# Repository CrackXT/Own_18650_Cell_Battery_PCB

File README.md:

# Own_18650_Cell_Battery_PCB

PCB files for a 18650 cell mount on a separate board

# Description

Compatible with protected 18650 cell type only!

This is an external battery cell board that allows you to mount the appropriate cell holder (18650) and thus have better connection and mounting options in your project or case.

The board can be produced here (AISLER) with the files (.brd and .sch) or by any other PCB manufacturer. -> https://aisler.net/

# Serie

- x

# Layout

Top<br>

Bottom<br>

Routing/Dimensions(inch)<br>

Schematic<br>
Schematic as .pdf at the top of the page.

# License

Open hardware, use it, mod it, whatever you want, feel free...

# Thanks!

Own design and layout.

# Version - Build

v1.3 - 18.06.2022

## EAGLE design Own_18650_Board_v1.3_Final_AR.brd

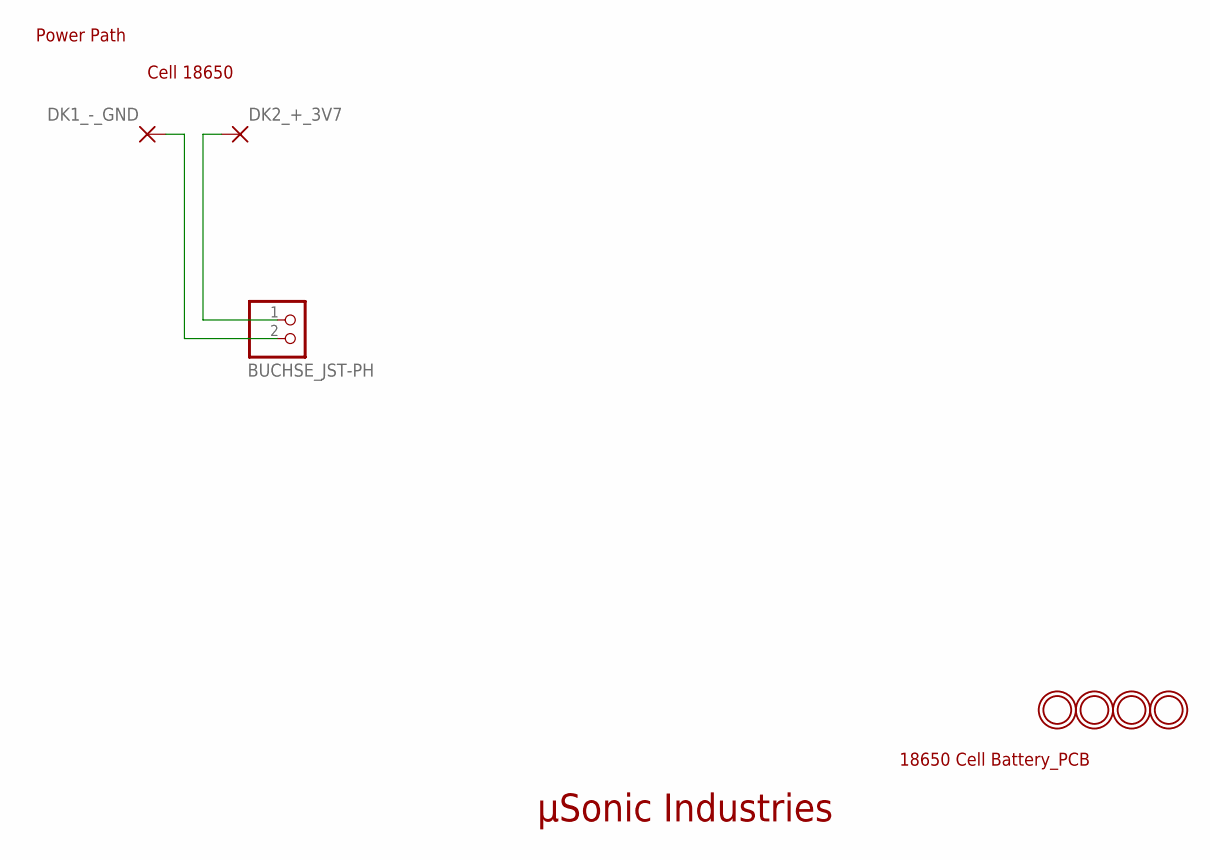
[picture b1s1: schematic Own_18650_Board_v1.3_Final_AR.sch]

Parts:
BUCHSE_JST-PH: JST_2PINOWN; JST-PH-2-THMOWN
DK1_-_GND, DK2_+_3V7: 3,17/1,3
U$1, U$2, U$3, U$5: MOUNTINGHOLE2.5; MOUNTINGHOLE_2.5_PLATED

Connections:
3V7: BUCHSE_JST-PH.1 (2), DK2_+_3V7.1
GND: BUCHSE_JST-PH.2 (1), DK1_-_GND.1

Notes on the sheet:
µSonic Industries
18650 Cell Battery_PCB
Power Path
Cell 18650

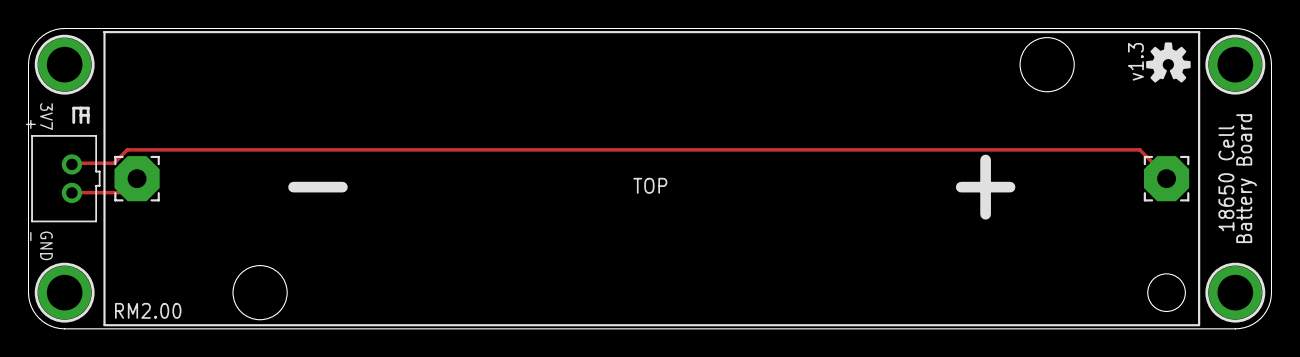
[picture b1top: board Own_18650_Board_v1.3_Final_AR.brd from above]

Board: 2 copper layers, 87.2 x 21.1 mm, 8 parts (0 on the bottom side), 2 nets.

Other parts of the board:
U$4: OSHW-LOGO-S

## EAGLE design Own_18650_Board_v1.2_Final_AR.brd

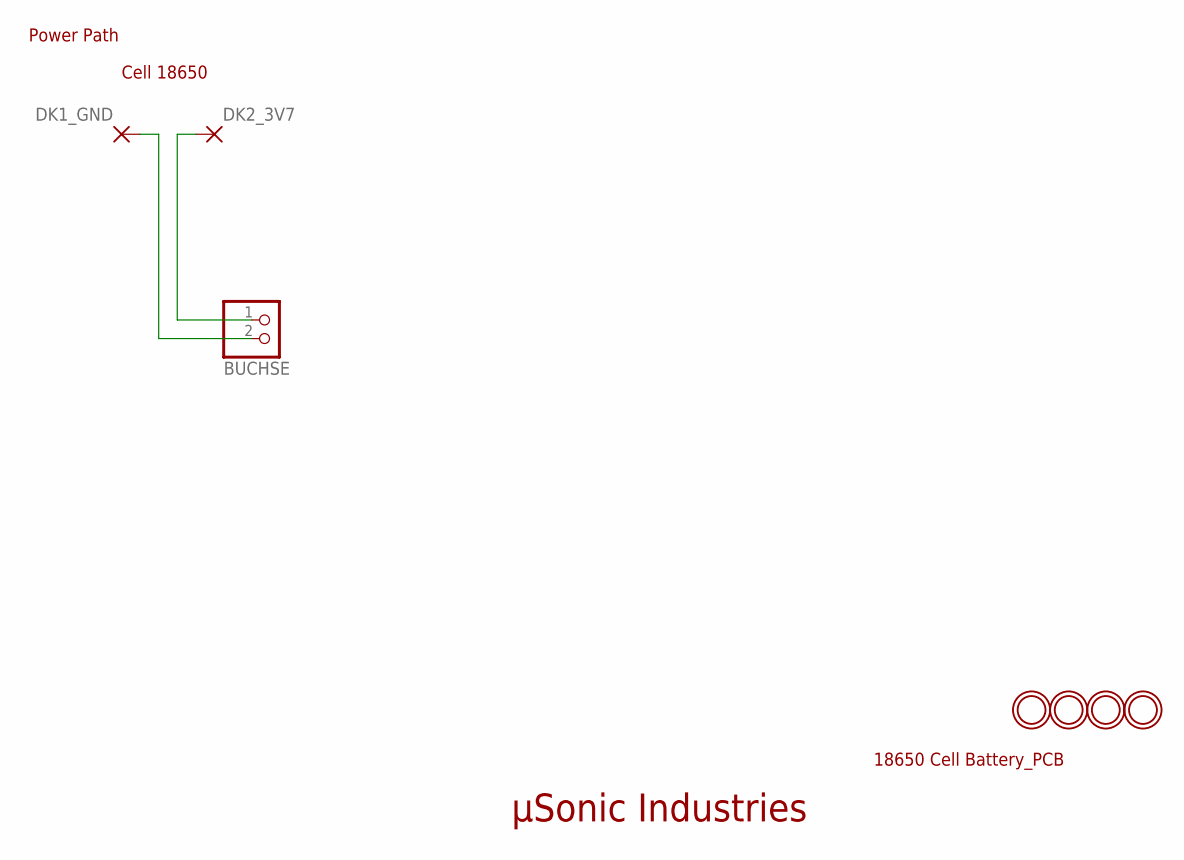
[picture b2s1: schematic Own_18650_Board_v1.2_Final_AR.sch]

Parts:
BUCHSE: JST_2PINOWN; JST-PH-2-THMOWN
DK1_GND, DK2_3V7: 3,17/1,3
U$1, U$2, U$3, U$5: MOUNTINGHOLE2.5; MOUNTINGHOLE_2.5_PLATED

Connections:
3V7: BUCHSE.1 (2), DK2_3V7.1
GND: BUCHSE.2 (1), DK1_GND.1

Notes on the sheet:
µSonic Industries
18650 Cell Battery_PCB
Power Path
Cell 18650

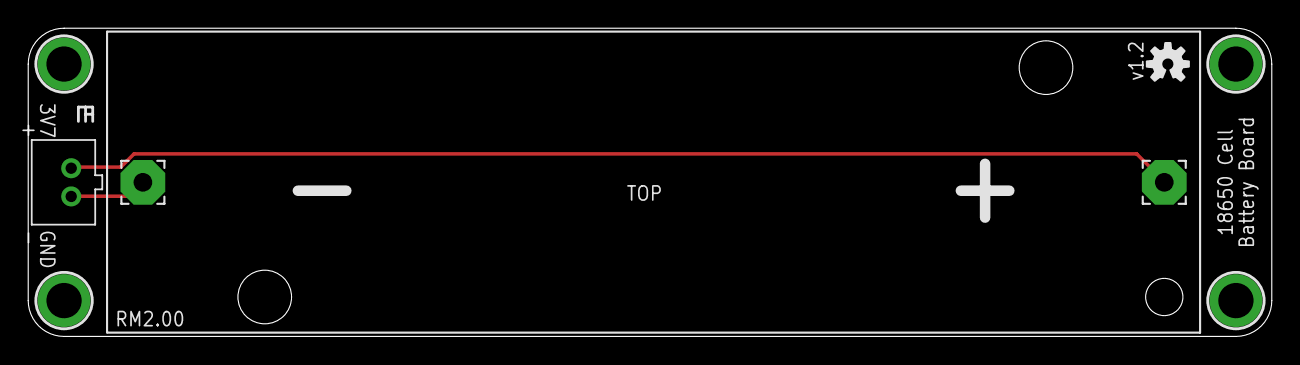
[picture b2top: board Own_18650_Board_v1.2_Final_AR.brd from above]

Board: 2 copper layers, 88.1 x 21.8 mm, 8 parts (0 on the bottom side), 2 nets.

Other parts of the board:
U$4: OSHW-LOGO-S

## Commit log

2022-06-21 Create history

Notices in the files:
parts and their libraries:
microbuilder: This work is placed in the public domain, and may be freely used for commercial and non-commercial work with the following conditions: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
SparkFun-Aesthetics: Licensing: Creative Commons ShareAlike 4.0 International - https://creativecommons.org/licenses/by-sa/4.0
